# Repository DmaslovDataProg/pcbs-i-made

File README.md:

# pcbs-i-made
You can find several PCBs that I have designed. 
# Breadboard power supply
Power supply two-layer Printed circuit Board(PCB) made from scratch that can be inserted in the breadboard and power both rails of the breadboard.

Power supply two-layer Printed circuit Board(PCB) made from scratch that can be inserted in the breadboard and power both rails of the breadboard.
## Tiny power supply 
A tiny solar power supply similar to those found in garden lights, but with a voltage regulator.

## Future implementations: 
1) Modify both PCB with the USB input.
2) Design MCU logger circuit.

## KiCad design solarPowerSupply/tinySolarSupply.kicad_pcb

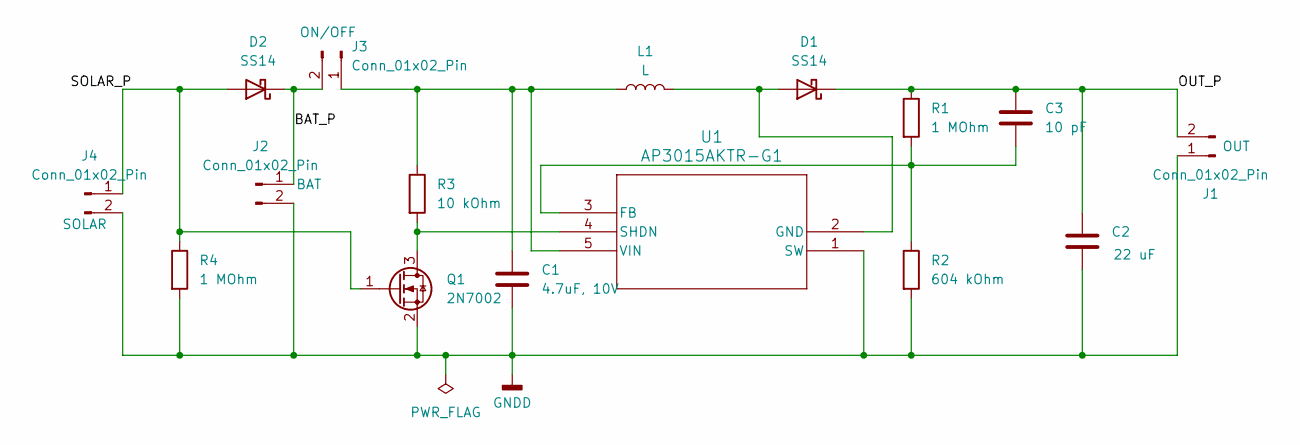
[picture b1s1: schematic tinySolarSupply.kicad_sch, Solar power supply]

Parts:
C1: 4.7uF, 10V; C_0805_2012Metric
C2: 22 uF; C_1206_3216Metric
C3: 10 pF; C_0805_2012Metric
D1, D2: SS14; D_SMA
J1, J2, J3: Conn_01x02_Pin; PinHeader_1x02_P2.54mm_Vertical
J4: Conn_01x02_Pin; PinHeader_1x02_P2.54mm_Horizontal
L1: L; L_Abracon_ASPI-0630LR
Q1: 2N7002; SOT-23
R1, R4: 1 MOhm; R_0805_2012Metric
R2: 604 kOhm; R_0805_2012Metric
R3: 10 kOhm; R_0805_2012Metric
U1: AP3015AKTR-G1; SOT23-5_1P55X2P9_DIO

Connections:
/BAT_P: D2.1 (K), J2.1, J3.2
/OUT_P: C2.1, C3.1, D1.1 (K), J1.2, R1.1
/SOLAR_P: D2.2 (A), J4.1, Q1.1 (G), R4.1
GNDD: C1.2, C2.2, J1.1, J2.2, J4.2, Q1.2 (S), R2.2, R4.2, U1.1 (SW)
unnamed: D1.2 (A), L1.2, U1.2 (GND)
unnamed: C1.1, J3.1, L1.1, R3.1, U1.5 (VIN)
unnamed: Q1.3 (D), R3.2, U1.4 (SHDN)
unnamed: C3.2, R1.2, R2.1, U1.3 (FB)

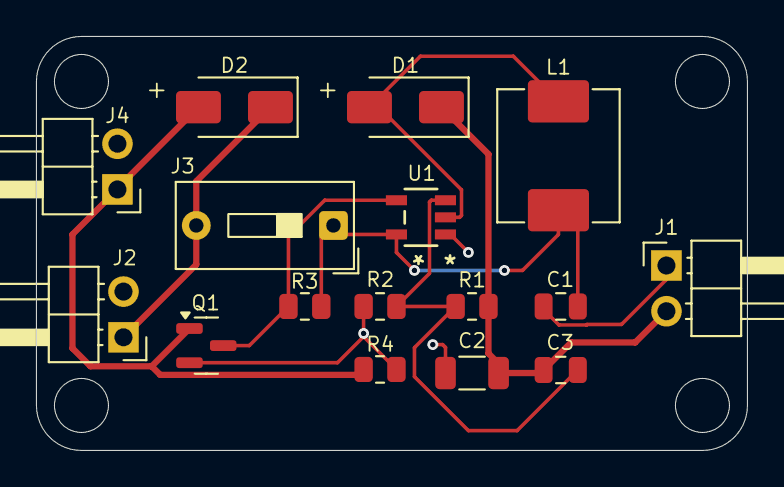
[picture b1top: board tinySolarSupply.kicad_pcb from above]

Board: 2 copper layers, 39.5 x 23.0 mm, 16 parts (0 on the bottom side), 8 nets.

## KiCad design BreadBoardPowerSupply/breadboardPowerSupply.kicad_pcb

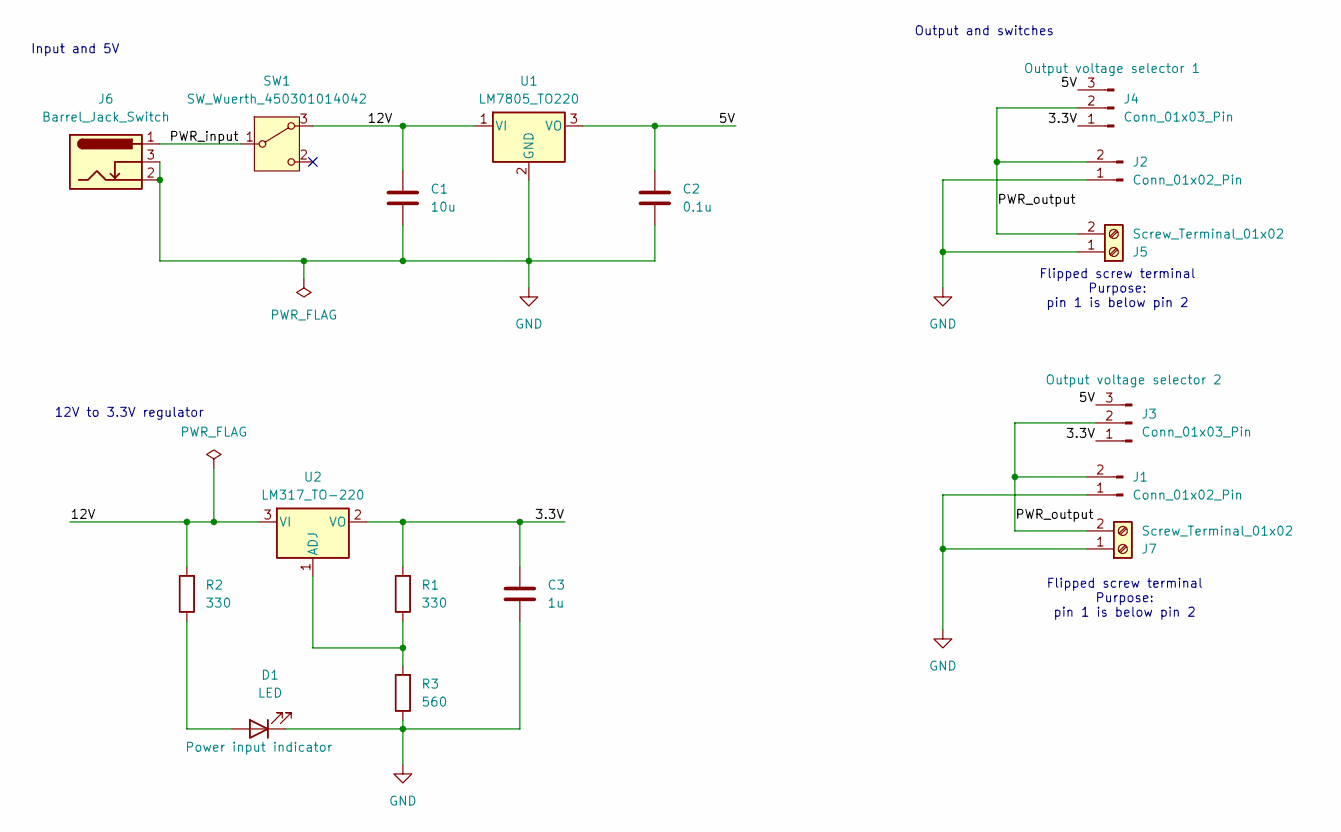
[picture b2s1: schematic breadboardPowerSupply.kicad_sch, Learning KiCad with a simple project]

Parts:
C1: 10u; C_Disc_D3.0mm_W1.6mm_P2.50mm
C2: 0.1u; C_Disc_D3.0mm_W1.6mm_P2.50mm
C3: 1u; C_Disc_D3.0mm_W1.6mm_P2.50mm
D1: LED; LED_D5.0mm
J1, J2: Conn_01x02_Pin; PinHeader_2x01_P2.54mm_Vertical
J3, J4: Conn_01x03_Pin; PinHeader_1x03_P2.54mm_Vertical
J5, J7: Screw_Terminal_01x02; TerminalBlock_bornier-2_P5.08mm
J6: Barrel_Jack_Switch; BarrelJack_Horizontal
R1, R2: 330; R_Axial_DIN0204_L3.6mm_D1.6mm_P7.62mm_Horizontal
R3: 560; R_Axial_DIN0204_L3.6mm_D1.6mm_P7.62mm_Horizontal
SW1: SW_Wuerth_450301014042; SW_Slide-03_Wuerth-WS-SLTV_10x2.5x6.4_P2.54mm
U1: LM7805_TO220; TO-220-3_Vertical
U2: LM317_TO-220; TO-220-3_Vertical

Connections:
/3.3V: C3.1, J3.1, J4.1, R1.2, U2.2 (VO)
/5V: C2.1, J3.3, J4.3, U1.3 (VO)
/12V: C1.2, R2.2, SW1.3 (A), U1.1 (VI), U2.3 (VI)
/PWR_input: J6.1, SW1.1 (B)
/PWR_output: J1.2, J2.2, J3.2, J4.2, J5.2, J7.2
GND: C1.1, C2.2, C3.2, D1.1 (K), J1.1, J2.1, J5.1, J6.2, J6.3, J7.1, R3.1, U1.2 (GND)
unnamed: D1.2 (A), R2.1
unnamed: R1.1, R3.2, U2.1 (ADJ)

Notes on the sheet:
Input and 5V
Output and switches
Flipped screw terminal Purpose: pin 1 is below pin 2
12V to 3.3V regulator

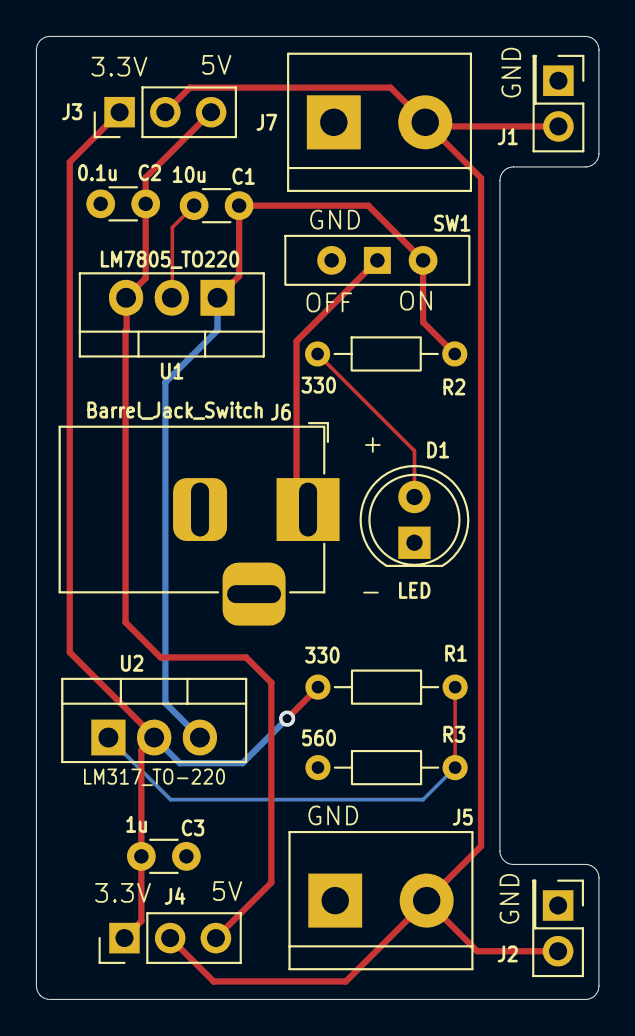
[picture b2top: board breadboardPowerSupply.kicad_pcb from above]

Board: 2 copper layers, 31.2 x 53.5 mm, 17 parts (0 on the bottom side), 8 nets.

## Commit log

2025-10-13 Initial commit with unwired PCB
2025-10-13 Routed PCB
2025-10-14 Silkscreen PCB
2025-10-15 Complete PCB
2025-10-15 Tiny solar power supply schematics and PCB design
2025-10-16 Tiny solar power supply complete schematics and gerber files
2025-10-16 uploaded images
